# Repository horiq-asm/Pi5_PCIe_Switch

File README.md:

Pi5のPCIeコネクタ情報が公開されたのでASM1184eをつないでPCIe　M.2コネクタ4portの動作検証しました。<br>
結論としては4ポート認識とA-keyの2.5GbpsLAN基板,M-keyの各種USB3基板が動作しました。<br>
ただし、M.2SSDがまだ現状認識できていません。　　＜＜対策済　<br>
pcie信号間クロストーク対策と、電源強化を行ってM.2SSDは正常に認識されました。<br>
回路図はまだ公開しませんが実験基板のpcdデータをKicadで公開します。<br>
<br>
youtubeに動作画面を載せています。<br>
https://youtu.be/G8ONZqBu1oo

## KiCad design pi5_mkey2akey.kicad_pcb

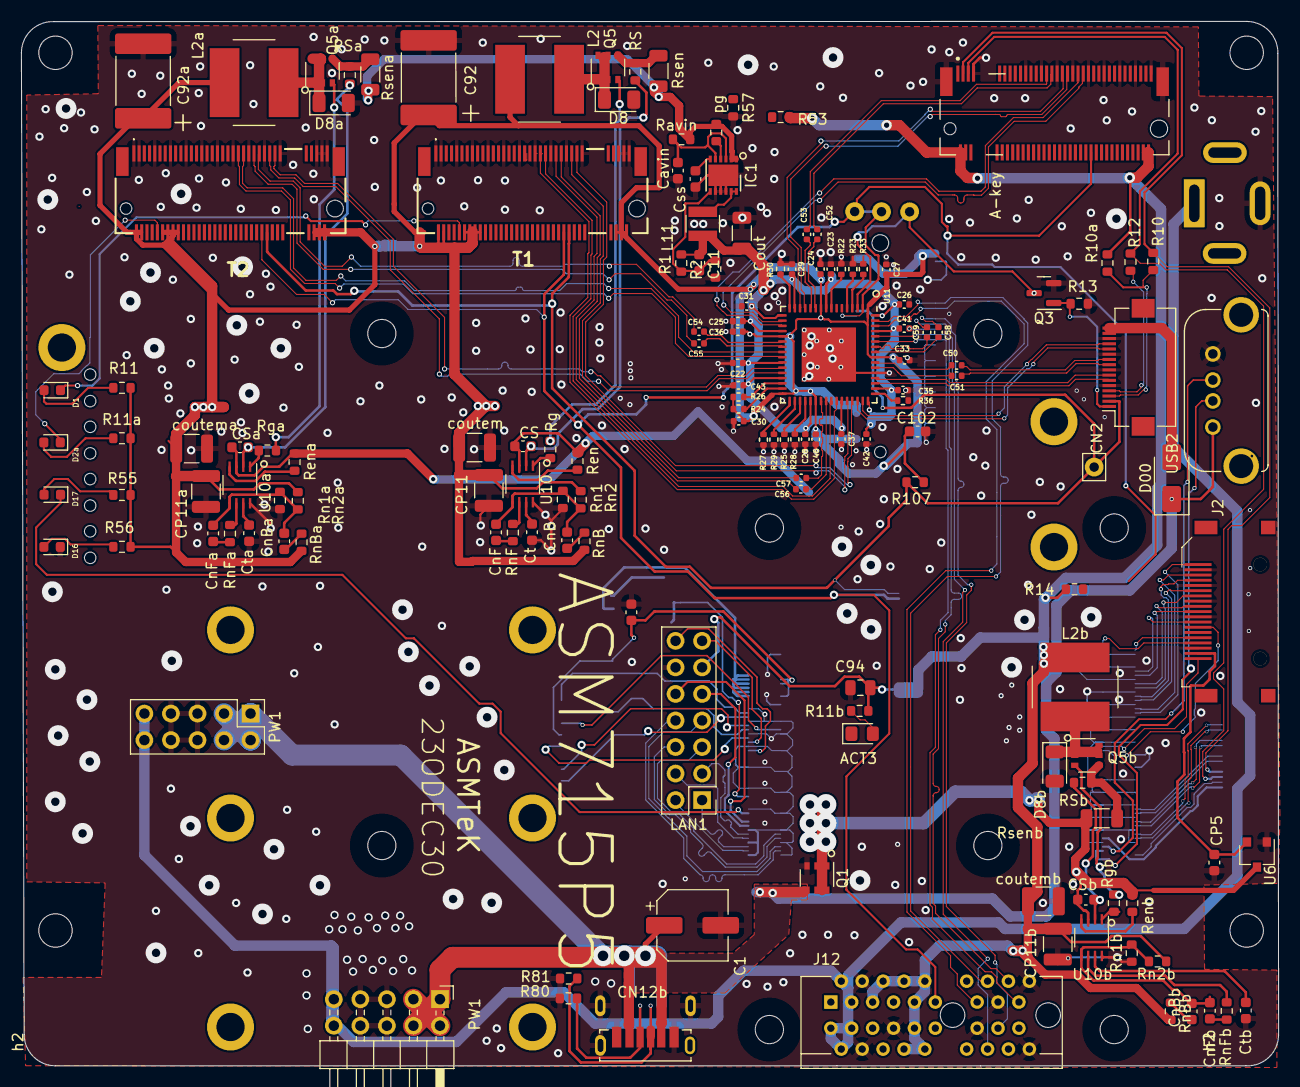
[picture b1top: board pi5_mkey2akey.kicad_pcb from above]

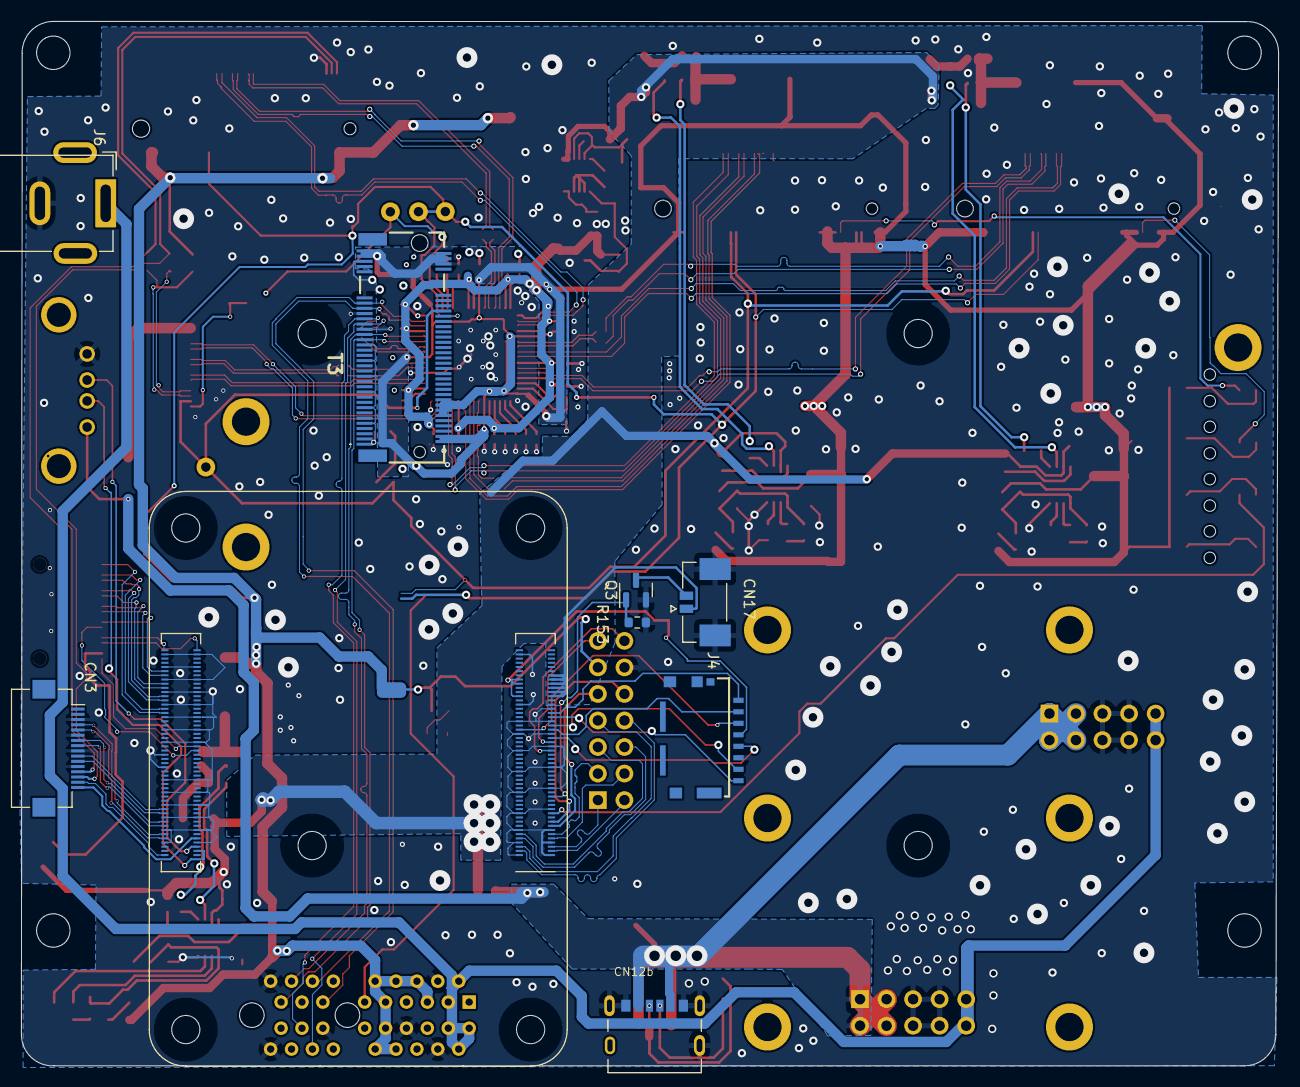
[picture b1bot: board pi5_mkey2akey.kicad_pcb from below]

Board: 2 copper layers, 120.3 x 100.0 mm, 167 parts (9 on the bottom side), 156 nets.

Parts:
C1: RSA0J331MCN1GS; CP_Elec_6.3x5.8
C11: 25p; C_0603_1608Metric
C22, C23, C24, C25, C26, C27, C28, C29, C30, C31, C33, C35, C36, C37, C41, C42, C43, C46, C50, C51, C52, C53, C54, C55, C56, C57, C58, C59: 100nF; C_0402_1005Metric
C92, C92a: ECASD40J476M025K00; C_2220_5650Metric_Pad1.97x5.40mm_HandSolder
C94: GRM188R61C106MAALD; C_0805_2012Metric
C102: 104; C_0603_1608Metric
CN2, CN3: Hirose_FH12-16S-0.5SH_1x16-1MP_P0.50mm_Horizontal
CN12b: CUI_UJC-VP-3-SMT-TR
CN12b#2: CUI_UJC-HP-3-SMT-TR
CN17: MOLEX_533980271
CP4: 100n; C_0603_1608Metric
CP5: 104; C_0603_1608Metric
CP11, CP11a, CP11b: C_1210_3225Metric
CS: 22n; C_0603_1608Metric
CSa: 22n; C_0603_1608Metric
CSb: 22n; C_0603_1608Metric
Cavin: 10n; C_0603_1608Metric
CnB: 220p; C_0603_1608Metric
CnBa: 220p; C_0603_1608Metric
CnBb: 220p; C_0603_1608Metric
CnF: 2.2n; C_0603_1608Metric
CnFa: 2.2n; C_0603_1608Metric
CnFb: 2.2n; C_0603_1608Metric
Cout: 22u; C_1206_3216Metric
Css: 470p; C_0603_1608Metric
Ct: 1n; C_0603_1608Metric
Cta: 1n; C_0603_1608Metric
Ctb: 1n; C_0603_1608Metric
D00: SR54F; D_SMA
D1, D2a: yellow; LED_0603_1608Metric
D1b: ACT3; LED_0805_2012Metric_Pad1.15x1.40mm_HandSolder
D8, D8a, D8b: SS2040FL; D_1206_3216Metric
D16: green; LED_0603_1608Metric
D17: red; LED_0603_1608Metric
IC1: RP510L00; DFN-12-1EP_3x3mm_P0.5mm_EP2.05x2.86mm
J2: HDMI_A_Female_2000-1-2-41-00-BK; HDMI
J4: 105162-0001
J6: BarrelJack_GCT_DCJ200-10-A_Horizontal
J12: 10018783-11200TLF; PCIex1-36
L2, L2a, L2b: SRN6045TA-4R7M; L_Bourns_SRN8040TA
L11: 1u; L_Abracon_ASPI-3012S
LAN1: PinHeader_2x07_P2.54mm_Vertical
Module1: ComputeModule4; Raspberry-Pi-4-Compute-Module
PW1: PinHeader_2x05_P2.54mm_Vertical
PW1#2: PinHeader_2x05_P2.54mm_Horizontal
Q1, Q5, Q5a, Q5b: SSM6J808R; TSOP-6_1.65x3.05mm_P0.95mm
Q3, Q3#2: BSS138-TP; SOT-23
R1, R2: 20k; R_0603_1608Metric
R10, R12: 0; R_0603_1608Metric
R10a: 2.2k; R_0603_1608Metric
R11, R11a, R11b, R55, R56, R153: 1k; R_0603_1608Metric
R13: 10k; R_0603_1608Metric
R14, R80, R81: 5.1k; R_0603_1608Metric
R22, R23, R25, R27: 1K; R_0402_1005Metric
R24, R26, R28, R29, R33: 10K; R_0402_1005Metric
R30, R36: 12.1K; R_0402_1005Metric
R53, R57: 51k; R_0603_1608Metric
R107: 100k; R_0603_1608Metric
RS: 20; R_0603_1608Metric
RSa: 20; R_0603_1608Metric
RSb: 20; R_0603_1608Metric
Ravin: 1; R_0603_1608Metric
Ren: 10k; R_0603_1608Metric
Rena: 10k; R_0603_1608Metric
Renb: 10k; R_0603_1608Metric
Rg: 20; R_0603_1608Metric
Rga: 20; R_0603_1608Metric
Rgb: 20; R_0603_1608Metric
Rn1, Rn1a, Rn1b: 10k; R_0603_1608Metric
Rn2, Rn2a, Rn2b: 30.9k; R_0603_1608Metric
RnB: 1k; R_0603_1608Metric
RnBa: 1k; R_0603_1608Metric
RnBb: 1k; R_0603_1608Metric
RnF: 8.2k; R_0603_1608Metric
RnFa: 8.2k; R_0603_1608Metric
RnFb: 8.2k; R_0603_1608Metric
Rsen: 27m; R_1206_3216Metric
Rsena: 27m; R_1206_3216Metric
Rsenb: 27m; R_1206_3216Metric
T1, T2, T3: MDT420M01001
T4: 2199230-8; b9973afb-34f9-4941-8c1f-dffebdb6dde0
U6: AP2331W; SC-59
U10, U10a, U10b: NJW4160R-TE2; SOT-23-8_Handsoldering
U11: ASM1184e; QFN-64-1EP_9x9mm_P0.5mm_EP5.2x5.2mm
USB2: USB-A-S-X-X-VT
coutem: C_1210_3225Metric
coutema: C_1210_3225Metric
coutemb: C_1210_3225Metric
h2, h2#2, h10, h15: MountingHole_3.2mm_M3
h4, h4#2, h6, h7: SLP3-150-100-F; MountingHole_2.1mm
h5, h5#2, h5#3, h5#4: MountingHole_1.1mm; MountingHole_2.1mm
pg: 100k; R_0603_1608Metric

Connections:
1v2: C11.2, C22.1, C23.1, C25.1, C26.1, C28.1, C29.1, C31.1, C35.1, C37.1, C41.1, C42.1, C43.1, Cout.1, L11.2, R1.2, U11.9 (1V2), U11.15 (1V2), U11.17 (1V2), U11.20 (1V2), U11.26 (1V2), U11.29 (1V2), U11.37 (1V2), U11.43 (1V2), U11.48 (1V2), U11.50 (1V2), U11.61 (1V2), U11.64 (1V2)
3.3V: C94.2, CP11b.2, J12.A5 (TCK), J12.A6 (TDI), J12.A8 (TMS), J12.A9 (+3.3V), J12.A10 (+3.3V), J12.B8 (+3.3v), J12.B9 (nTRST), J12.B10 (+3.3vAUX), L2b.2, LAN1.11, R10a.1, R11b.2, R14.1, R53.1, Rn2b.1, RnBb.1, T4.2, T4.4, T4.72, T4.74, coutemb.1
3.3vema: C24.1, C27.1, C30.1, C33.1, C36.1, C46.1, C92.1, C92a.1, C102.1, CP11.2, CP11a.2, L2.2, L2a.2, R11.2, R11a.2, R24.1, R26.1, R55.2, R56.2, R107.2, Rn2.1, Rn2a.1, RnB.1, RnBa.1, T1.2, T1.4, T1.12, T1.14, T1.16, T1.18, T1.70, T1.72, T1.74, T2.2, T2.4, T2.12, T2.14, T2.16, T2.18, T2.70, T2.72, T2.74, T3.2, T3.4, T3.12, T3.14, T3.16, T3.18, T3.70, T3.72, T3.73, T3.74, T3.75, U11.1 (3V_AUX), U11.10 (3V3), U11.21 (3V3), U11.32 (3V3), U11.38 (3V3), U11.56 (3V3), coutem.1, coutema.1
5VIN: C1.1, CN12b.A9, CN12b.B9, CN12b#2.A9, CN12b#2.B9, D00.1, PW1.1, PW1.2, PW1.3, PW1.4, PW1#2.1, PW1#2.2, PW1#2.3, PW1#2.4, Q1.4, USB2.1
12V: J6.1, J12.A2 (+12V), J12.A3 (+12V), J12.B1 (+12v), J12.B2 (+12v), J12.B3 (+12v), PW1.9, PW1.10, PW1#2.9, PW1#2.10
1184e_TX_N: C51.2, U11.54 (TXP_IN)
1184e_TX_P: C50.2, U11.55 (TXN_IN)
A5: CN12b.A5, CN12b#2.B5, R81.1
B5: CN12b.B5, CN12b#2.A5, R80.1
Ethernet_Pair0_N: LAN1.6, Module1.10 (Ethernet_Pair0_N)
Ethernet_Pair0_P: LAN1.5, Module1.12 (Ethernet_Pair0_P)
Ethernet_Pair1_N: LAN1.7, Module1.6 (Ethernet_Pair1_N)
Ethernet_Pair1_P: LAN1.8, Module1.4 (Ethernet_Pair1_P)
Ethernet_Pair2_N: LAN1.4, Module1.9 (Ethernet_Pair2_N)
Ethernet_Pair2_P: LAN1.3, Module1.11 (Ethernet_Pair2_P)
Ethernet_Pair3_N: LAN1.1, Module1.5 (Ethernet_Pair3_N)
Ethernet_Pair3_P: LAN1.2, Module1.3 (Ethernet_Pair3_P)
Ethernet_nLED2: LAN1.10, Module1.17 (Ethernet_nLED2(3.3v))
Ethernet_nLED3: LAN1.9, Module1.15 (Ethernet_nLED3(3.3v))
GND: C1.2, C22.2, C23.2, C24.2, C25.2, C26.2, C27.2, C28.2, C29.2, C30.2, C31.2, C33.2, C35.2, C36.2, C37.2, C41.2, C42.2, C43.2, C46.2, C92.2, C92a.2, C94.1, C102.2, CN2.5, CN2.8, CN2.11, CN2.14, CN3.3, CN3.6, CN3.9, CN3.12, CN12b.A12, CN12b.B12, CN12b.S1, CN12b#2.A12, CN12b#2.B12, CN12b#2.S1, CN12b#2.S2, CN12b#2.S4, CN17.S1, CN17.S2, CP4.1, CP5.1, CP11.1, CP11a.1, CP11b.1, Cavin.1, Cout.2, Css.1, Ct.2, Cta.2, Ctb.2, D8.2, D8a.2, D8b.2, D16.1, IC1.8, IC1.9, IC1.10, IC1.13, J2.2, J2.5, J2.8, J2.11, J2.17, J4.6, J6.2, J12.A4 (GND), J12.A15 (GND), J12.A18 (GND), J12.B4 (GND), J12.B7 (GND), J12.B13 (GND), J12.B18 (GND), LAN1.12, Module1.1 (GND), Module1.2 (GND), Module1.7 (GND), Module1.8 (GND), Module1.13 (GND), Module1.14 (GND), Module1.22 (GND), Module1.23 (GND), Module1.32 (GND), Module1.33 (GND), Module1.42 (GND), Module1.43 (GND), Module1.52 (GND), Module1.53 (GND), Module1.59 (GND), Module1.60 (GND), Module1.65 (GND), Module1.66 (GND), Module1.71 (GND), Module1.74 (GND), Module1.98 (GND), Module1.107 (GND), Module1.108 (GND), Module1.113 (GND), Module1.114 (GND), Module1.119 (GND), Module1.120 (GND), Module1.125 (GND), Module1.126 (GND), Module1.131 (GND), Module1.132 (GND), Module1.137 (GND), Module1.138 (GND), Module1.144 (GND), Module1.150 (GND), Module1.155 (GND), Module1.156 (GND), Module1.161 (GND), Module1.162 (GND), Module1.167 (GND), Module1.168 (GND), Module1.173 (GND), Module1.174 (GND), Module1.179 (GND), Module1.180 (GND), Module1.185 (GND), Module1.186 (GND), Module1.191 (GND), Module1.192 (GND), Module1.197 (GND), Module1.198 (GND), PW1.5, PW1.6, PW1.7, PW1.8, PW1#2.5, PW1#2.6, PW1#2.7, PW1#2.8, Q1.3, Q3.2, Q3#2.2, R2.1, R13.2, R22.2, R23.2, R25.2, R27.2, R28.1, R29.1, R30.2, R33.1, R36.2, R57.1, R80.2, R81.2, R153.1, Rn1.2, Rn1a.2, Rn1b.2, T1.1, T1.3, T1.9, T1.15, T1.21, T1.27, T1.33, T1.39, T1.45, T1.51, T1.57, T1.71, T1.73, T1.75, T2.1, T2.3, T2.9, T2.15, T2.21, T2.27, T2.33, T2.39, T2.45, T2.51, T2.57, T2.71, T2.73, T2.75, T3.1, T3.3, T3.9, T3.15, T3.21, T3.27, T3.33, T3.39, T3.45, T3.51, T3.57, T3.71, T4.7, T4.27, T4.33, T4.39, T4.45, T4.51, T4.57, T4.63, T4.69, T4.75, T4.S1, T4.S2, U6.1, U10.8, U10a.8, U10b.8, U11.53 (GND), U11.65 (GND), USB2.4, coutem.2, coutema.2, coutemb.2
GPIO14: LAN1.13, Module1.55 (GPIO14)
GPIO15: LAN1.14, Module1.51 (GPIO15)
GPIO16: Module1.29 (GPIO16), Q3#2.1, R153.2
H5V: CP5.2, J2.18, U6.2
HDMI0_CEC: J2.13, Module1.151 (HDMI0_CEC)
HDMI0_CLK_N: J2.12, Module1.190 (HDMI0_CLK_N)
HDMI0_CLK_P: J2.10, Module1.188 (HDMI0_CLK_P)
HDMI0_SCL: J2.15, Module1.200 (HDMI0_SCL)
HDMI0_SDA: J2.16, Module1.199 (HDMI0_SDA)
HDMI0_TX0_N: J2.9, Module1.184 (HDMI0_TX0_N)
HDMI0_TX0_P: J2.7, Module1.182 (HDMI0_TX0_P)
HDMI0_TX1_N: J2.6, Module1.176 (HDMI0_TX1_P)
HDMI0_TX1_P: J2.4, Module1.178 (HDMI0_TX1_N)
HDMI0_TX2_N: J2.3, Module1.172 (HDMI0_TX2_N)
HDMI0_TX2_P: J2.1, Module1.170 (HDMI0_TX2_P)
HDMI_HOTPLUG: J2.19, Module1.153 (HDMI0_HOTPLUG)
HS3R+: CN2.3, R10.2, R10a.2
HS3R-: CN2.4, R12.2
HS3RN: CN3.14, R12.1, T4.5
HS3RP: CN3.13, R10.1, T4.3
MT1: CN17.2, Q3#2.3
NJ001: Rg.2, U10.1
NJ_g: Q5.3, Rg.1
Nj002: CS.2, RS.2, U10.2
Nj003: CnB.1, RnB.2
Nj005: CnB.2, CnF.2, Rn1.1, Rn2.2, U10.5
Nj007: Q5.4, RS.1, Rsen.2
Nj008: D8.1, L2.1, Q5.1, Q5.2, Q5.5, Q5.6
Nj009: RnF.1, U10.6
Nj010: CnF.1, RnF.2
Nj011: Ct.1, U10.7
Njen: Ren.2, U10.4
PCIE_CLK_2N: CN3.4, Module1.112 (PCIe_CLK_N)
PCIE_CLK_2P: CN3.5, Module1.110 (PCIe_CLK_P)
PCIE_CLK_nREQ2: CN3.15, Module1.102 (PCIe_CLK_nREQ)
PCIE_RX_2N: CN3.7, Module1.118 (PCIe_RX_N)
PCIE_RX_2P: CN3.8, Module1.116 (PCIe_RX_P)
PCIE_TX_2N: CN3.10, Module1.124 (PCIe_TX_N)
PCIE_TX_2P: CN3.11, Module1.122 (PCIe_TX_P)
PCIe_CLK_N: CN2.13, U11.47 (REFCLKN_IN)
PCIe_CLK_P: CN2.12, U11.46 (REFCLKP_IN)
PCIe_CLK_nREQ: CN2.2, R107.1, T1.52, T2.52, T3.52
PCIe_RX_N: C51.1, CN2.9
PCIe_RX_P: C50.1, CN2.10
PCIe_TX_N: CN2.6, U11.51 (RXP_IN)
PCIe_TX_P: CN2.7, U11.52 (RXN_IN)
PCIe_nRST: CN3.16, Module1.109 (PCIe_nRST)
Pi5_pRST: CN2.1, Q3.1, R13.1
Pi_nLED_Activity: D17.1, Module1.21 (PI_nLED_Activity)
RSTI: Q3.3, U11.3 (RES_IN)
RSTO: J12.A11 (nPERST), R14.2, T1.50, T2.50, T3.50, T4.52, U11.2 (RES_OUT)
SD_CLK: J4.5, Module1.57 (SD_CLK)
SD_CMD: J4.3, Module1.62 (SD_CMD)
SD_DATA0: J4.7, Module1.63 (SD_DAT0)
SD_DATA1: J4.8, Module1.67 (SD_DAT1)
SD_DATA2: J4.1, Module1.69 (SD_DAT2)
SD_DATA3: J4.2, Module1.61 (SD_DAT3)
SD_PWR: CP4.2, J4.4, Module1.78 (GPIO_VREF(1.8v/3.3v_Input)), Module1.84 (+3.3v_(Output)), Module1.86 (+3.3v_(Output))
USB_N: Module1.103 (USB2_N), USB2.2
USB_P: Module1.105 (USB2_P), USB2.3
VCC-2: CN17.1, CS.1, CSa.1, CSb.1, IC1.1, IC1.2, Module1.77 (+5v_(Input)), Module1.79 (+5v_(Input)), Module1.81 (+5v_(Input)), Module1.83 (+5v_(Input)), Module1.85 (+5v_(Input)), Module1.87 (+5v_(Input)), Q1.1, Q1.2, Q1.5, Q1.6, Ravin.2, Ren.1, Rena.1, Renb.1, Rsen.1, Rsena.1, Rsenb.1, U6.3, U10.3, U10a.3, U10b.3, pg.2
aNj001: Rga.2, U10a.1
aNj002: CSa.2, RSa.2, U10a.2
aNj003: CnBa.1, RnBa.2
aNj005: CnBa.2, CnFa.2, Rn1a.1, Rn2a.2, U10a.5
aNj007: Q5a.4, RSa.1, Rsena.2
aNj008: D8a.1, L2a.1, Q5a.1, Q5a.2, Q5a.5, Q5a.6
aNj009: RnFa.1, U10a.6
aNj010: CnFa.1, RnFa.2
aNj011: Cta.1, U10a.7
aNj_g: Q5a.3, Rga.1
aNjen: Rena.2, U10a.4
bNj001: Rgb.2, U10b.1
bNj002: CSb.2, RSb.2, U10b.2
bNj003: CnBb.1, RnBb.2
bNj005: CnBb.2, CnFb.2, Rn1b.1, Rn2b.2, U10b.5
bNj007: Q5b.4, RSb.1, Rsenb.2
bNj008: D8b.1, L2b.1, Q5b.1, Q5b.2, Q5b.5, Q5b.6
bNj009: RnFb.1, U10b.6
bNj010: CnFb.1, RnFb.2
bNj011: Ctb.1, U10b.7
bNj_g: Q5b.3, Rgb.1
bNjen: Renb.2, U10b.4
bm3das: D1b.1 (K), T3.10
exPWR: CN2.15, CN2.16, D00.2
exPWR2: CN3.1, CN3.2
fclk1+: T4.49, U11.18 (REFCLKP_1)
fclk1-: T4.47, U11.19 (REFCLKN_1)
fclk2+: T2.55, U11.27 (REFCLKP_2)
fclk2-: T2.53, U11.28 (REFCLKN_2)
fclk3+: T1.53, U11.44 (REFCLKP_3)
fclk3-: T1.55, U11.45 (REFCLKN_3)
fclk4+: J12.A13 (REFCLK+), T3.53, U11.62 (REFCLKP_4)
fclk4-: J12.A14 (REFCLK-), T3.55, U11.63 (REFCLKN_4)
h003: R33.2, U11.4 (GPIO_0)
h004: R23.1, U11.5 (GPIO_2)
h005: R22.1, U11.8 (GPIO_4)
h012: R30.1, U11.16 (REXT1)
h025: R26.2, U11.30 (GPIO_5)
h026: R24.2, U11.31 (GPIO_1)
h027: R27.1, U11.33 (TEST_EN)
h028: R29.2, U11.34 (GPIO_3)
h029: R25.1, U11.35 (GPIO_6)
h030: R28.2, U11.36 (GPIO_7)
m002: Cavin.2, IC1.3, IC1.5, Ravin.1
m003: IC1.4, pg.1
m3das: D1.1, T1.10
m3das2: D2a.1, T2.10
m004: Css.2, IC1.6
m005: C11.1, IC1.7, R1.1, R2.2
m006: IC1.11, IC1.12, L11.1
rext2: R36.1, U11.49 (REXT2)
rx1+: T4.43, U11.13 (RXP_1)
rx1-: T4.41, U11.14 (RXN_1)
rx2+: T2.43, U11.24 (RXP_2)
rx2-: T2.41, U11.25 (RXN_2)
rx3+: T1.43, U11.41 (RXP_3)
rx3-: T1.41, U11.42 (RXN_3)
rx4+: J12.A17 (PERN0), T3.41, U11.59 (RXP_4)
rx4-: J12.A16 (PERP0), T3.43, U11.60 (RXN_4)
tx1+: C52.2, U11.11 (TXP_1)
tx1-: C53.2, U11.12 (TXN_1)
tx1c+: C52.1, T4.37
tx1c-: C53.1, T4.35
tx2+: C54.2, U11.22 (TXP_2)
tx2-: C55.2, U11.23 (TXN_2)
tx2c+: C54.1, T2.49
tx2c-: C55.1, T2.47
tx3+: C57.2, U11.39 (TXP_3)
tx3-: C56.2, U11.40 (TXN_3)
tx3c+: C57.1, T1.49
tx3c-: C56.1, T1.47
tx4+: C58.2, U11.57 (TXP_4)
tx4-: C59.2, U11.58 (TXN_4)
tx4c+: C58.1, J12.B15 (PETN0), T3.49
tx4c-: C59.1, J12.B14 (PETP0), T3.47
